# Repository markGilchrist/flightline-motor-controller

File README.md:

# ESP32-S3 12 V Motor PWM Controller (rev 1.0)

A 92 × 76 mm two-layer board that runs a 12 V DC motor from a car battery (11–14.4 V).
An ESP32-S3 sets the motor speed and adds pauses using PWM into a low-side MOSFET.

```
 Car battery ─► J1 ─► 15 A blade fuse ─► TVS (load-dump) ─► reverse-polarity P-FET ─► V12 rail
                                                                                      │
                       ┌──────────── 3.3 V buck (LMR33630) ◄── V12 or USB-C 5 V ──────┤
                       ▼                                                              ▼
                 ESP32-S3-WROOM-1 ── GPIO4 PWM ──► UCC27517 gate driver ──► N-MOSFET ──► J2 MOTOR −
                       │                                                     J2 MOTOR + ◄── V12
                       └── GPIO1 battery-voltage sense, GPIO2 status LED, USB-C for programming
```

## What's in this folder

| File | What it is |
|---|---|
| `motor_ctrl.kicad_pro / .kicad_sch / .kicad_pcb` | KiCad project (opens in KiCad 7, 8 or 9). Ground pours are already filled. |
| `motor_ctrl.kicad_sym`, `sym-lib-table` | The project's schematic symbols, so KiCad finds and can edit them |
| `motor_ctrl_schematic.pdf` | Schematic as a PDF (plotted by KiCad) |
| `fab/gerbers/` | **Ready-to-order** Gerbers, drill files and drill maps |
| `fab/motor_ctrl_pos.csv` | Pick-and-place file (mm, origin at the board's bottom-left corner) |
| `motor_ctrl_BOM.csv` | Bill of materials |
| `board_top.png`, `board_bottom.png` | Renders of the Gerber files (top and bottom copper, silkscreen, drills) |
| `firmware/motor_pwm/motor_pwm.ino` | Arduino sketch: speed program with ramps and pauses |
| `firmware/test/` | Host-side tests for the sketch's logic (`sh firmware/test/run_tests.sh`, needs g++) |

## Key specs

- **Input:** 11–14.4 V car battery. Survives reverse battery (P-MOSFET Q1) and load-dump spikes (SMCJ20CA TVS clamps to about 32 V; everything on the 12 V side is rated 35–45 V).
- **Motor output:** 12 V, up to **10 A continuous**, fused at 15 A. Q2 (IPD90N04S4L-04, 3.8 mΩ) switches the motor's negative lead to ground, so the motor always sees full battery voltage scaled by the duty cycle.
- **PWM:** 20 kHz (silent), 10-bit, from GPIO4 through a UCC27517 4 A gate driver, so the MOSFET switches cleanly from a 3.3 V pin. R5 holds the motor **off** while the ESP32 boots or resets.
- **Freewheel diode:** D3 (STPS20L45CG, 2 × 10 A Schottky) across the motor absorbs the inductive kick at every PWM edge.
- **Logic power:** LMR33630 synchronous buck, 3.3 V / 3 A, runs from the battery or from USB-C. You can program the board on the bench with only a USB cable; the motor won't run without 12 V.
- **Wiper park input:** J5 takes the motor's park-switch contact (12 V tolerant, read on GPIO7), so pauses can stop the blades in the parked position.
- **Extras:** battery-voltage sense on GPIO1 (low/high-voltage cut-out in firmware), status LED on GPIO2, power LED, RESET and BOOT buttons, and a 4-pin AUX header (3V3, GPIO5, GPIO6, GND) for a speed pot, button or sensor.

## Wiring

| Terminal | Pin 1 | Pin 2 |
|---|---|---|
| **J1 BATTERY** | +12 V (from battery +) | GND (battery −) |
| **J2 MOTOR** | MOTOR − | MOTOR + (+12 V) |
| **J5 PARK** | Park-switch contact | GND |

Use wire rated for your motor current (1.5 mm² / 16 AWG for 10 A), keep the battery leads short, and add an inline fuse at the battery end of the + lead as well.

### Using a windscreen wiper motor

- Connect J2 pin 2 (+12 V) to the motor's **low-speed** terminal and J2 pin 1 (MOTOR −) to its **ground/common** terminal. Leave the high-speed terminal unconnected. Terminal numbering varies between makers, so identify them on a bench supply first.
- **Mounting:** the board switches the motor's negative wire. If the motor's ground terminal is connected to its metal case, the case must not touch anything wired to battery negative (a metal frame, a car body). Otherwise the motor gets its ground directly and the board can't stop it. Check with a meter between the ground terminal and the case.
- Typical currents: 2–8 A running, 15–30 A if the arm is jammed or frozen. A jam blows the 15 A fuse within a few seconds, which protects the board.

**Park switch (J5).** With it connected, every pause, `stop` command and the pot turned to zero first runs the wiper on to its park position, then stops.

- **Park contact that closes to ground at park:** wire it between J5 pin 1 and J5 pin 2 (GND).
- **Car-style motor with a 31b park terminal** (it switches between 53a and the motor's ground): wire **31b to J5 pin 1** only. 53a can stay unconnected.
- **Contact that opens at park:** wire it like the first case and set `PARK_INVERT = true` in the sketch.
- To check the wiring, send `v` over USB serial with 12 V connected. It reports the park-input voltage and whether it reads "at park". Move the blades by hand, or run the motor slowly with `s 30`, and watch it change.
- If the firmware never sees the park position within 6 s (for example J5 isn't wired), it stops the motor where it is and prints a warning. Set `USE_PARK = false` if you don't use the park switch.

## Making the board

1. Zip the contents of `fab/gerbers/` and upload it to any PCB service (JLCPCB, PCBWay, OSH Park, Aisler…). Check the preview the fab shows you against `board_top.png` / `board_bottom.png`.
2. Order with **2 oz copper** and 1.6 mm thickness. The 10 A rating depends on the 4 mm power tracks being 2 oz.
3. Board checks already done in KiCad: DRC has no copper, clearance or courtyard errors and no unconnected pads. The only remaining items are four silkscreen warnings from the inductor L1's own library outline, which the fab trims automatically. ERC has 0 errors and 0 warnings, and the schematic and board netlists match.
4. If you change the board in KiCad, press **B** to refill the pours, rerun **Inspect → Design Rules Checker**, and plot new Gerbers with **File → Fabrication Outputs**.
5. All parts are standard footprints from the BOM. The SMD parts are 0603/0805 or larger, so you can hand-solder them. The SO-PowerPAD (U1) and the DPAK/D2PAK tabs need hot air or a hot plate.

## Firmware

1. Arduino IDE → install **esp32 by Espressif** (core 3.x).
2. Board: **ESP32S3 Dev Module**, **USB CDC On Boot: Enabled**.
3. Plug in USB-C. If the port doesn't appear, hold **BOOT**, tap **RESET**, release **BOOT**.
4. Upload `motor_pwm.ino`.

### Using the FlightLine Controller app

The board works with the **FlightLine Controller** app (iOS and Android). It advertises over Bluetooth as **Flightline**, so switch it on and it appears as a card in the app.

- **Off/On (normal cycle):** runs at the set speed for the on time, parks the wiper, waits the off time, and repeats.
- **Quick Burst:** runs continuously at the set speed until you switch it off.
- **Speed, On Time, Off Time sliders:** take effect straight away.
- The board saves the speed, times and Off/On switch, so after a power cut it carries on as it was. Quick Burst always starts off.
- The board shows up in the app as a **Flapper**. To make it a **Magnet** (Off/On just runs at the set speed, with no on/off times) or a **French flapper**, change `FL_DEVICE_TYPE` near the top of the sketch to 2 or 3.

The same commands also work over USB serial (115200 baud), one per line, which is handy for testing without a phone. For example, `aS128` sets the speed to 128/255 and `aS?bb` asks for it back. The full list is at the top of the sketch.

Also over USB: `s 50` runs the motor at 50 % (manual), `stop` parks and stops, `r 500` sets the ramp time for `s` in ms, and `v` prints the battery and park-input voltages, the mode and the Bluetooth state. `go` runs the built-in step program in the `program[]` table (speed, ramp time and hold time per step; speed 0 is a pause). Any app command switches back to app control.

If the battery drops below 10.5 V or rises above 16 V, the motor stops and the status LED blinks fast. It restarts on its own once the battery is back between 11.5 V and 15.5 V, ramping up from zero rather than jumping straight back to speed. On USB power alone the firmware sees no battery, so the motor stays off.

## Before you power it up

- Check the motor's **stall current**. A motor that draws more than about 15 A at start-up will blow the fuse. The MOSFET and diode can handle the surge; the fuse is there to protect the wiring.
- First power-up: use a current-limited bench supply at 12 V, no motor, and check that the 3.3 V rail and the power LED are OK. Then connect the motor.
- The motor's + lead is live whenever the battery is connected. PWM only switches the − side.

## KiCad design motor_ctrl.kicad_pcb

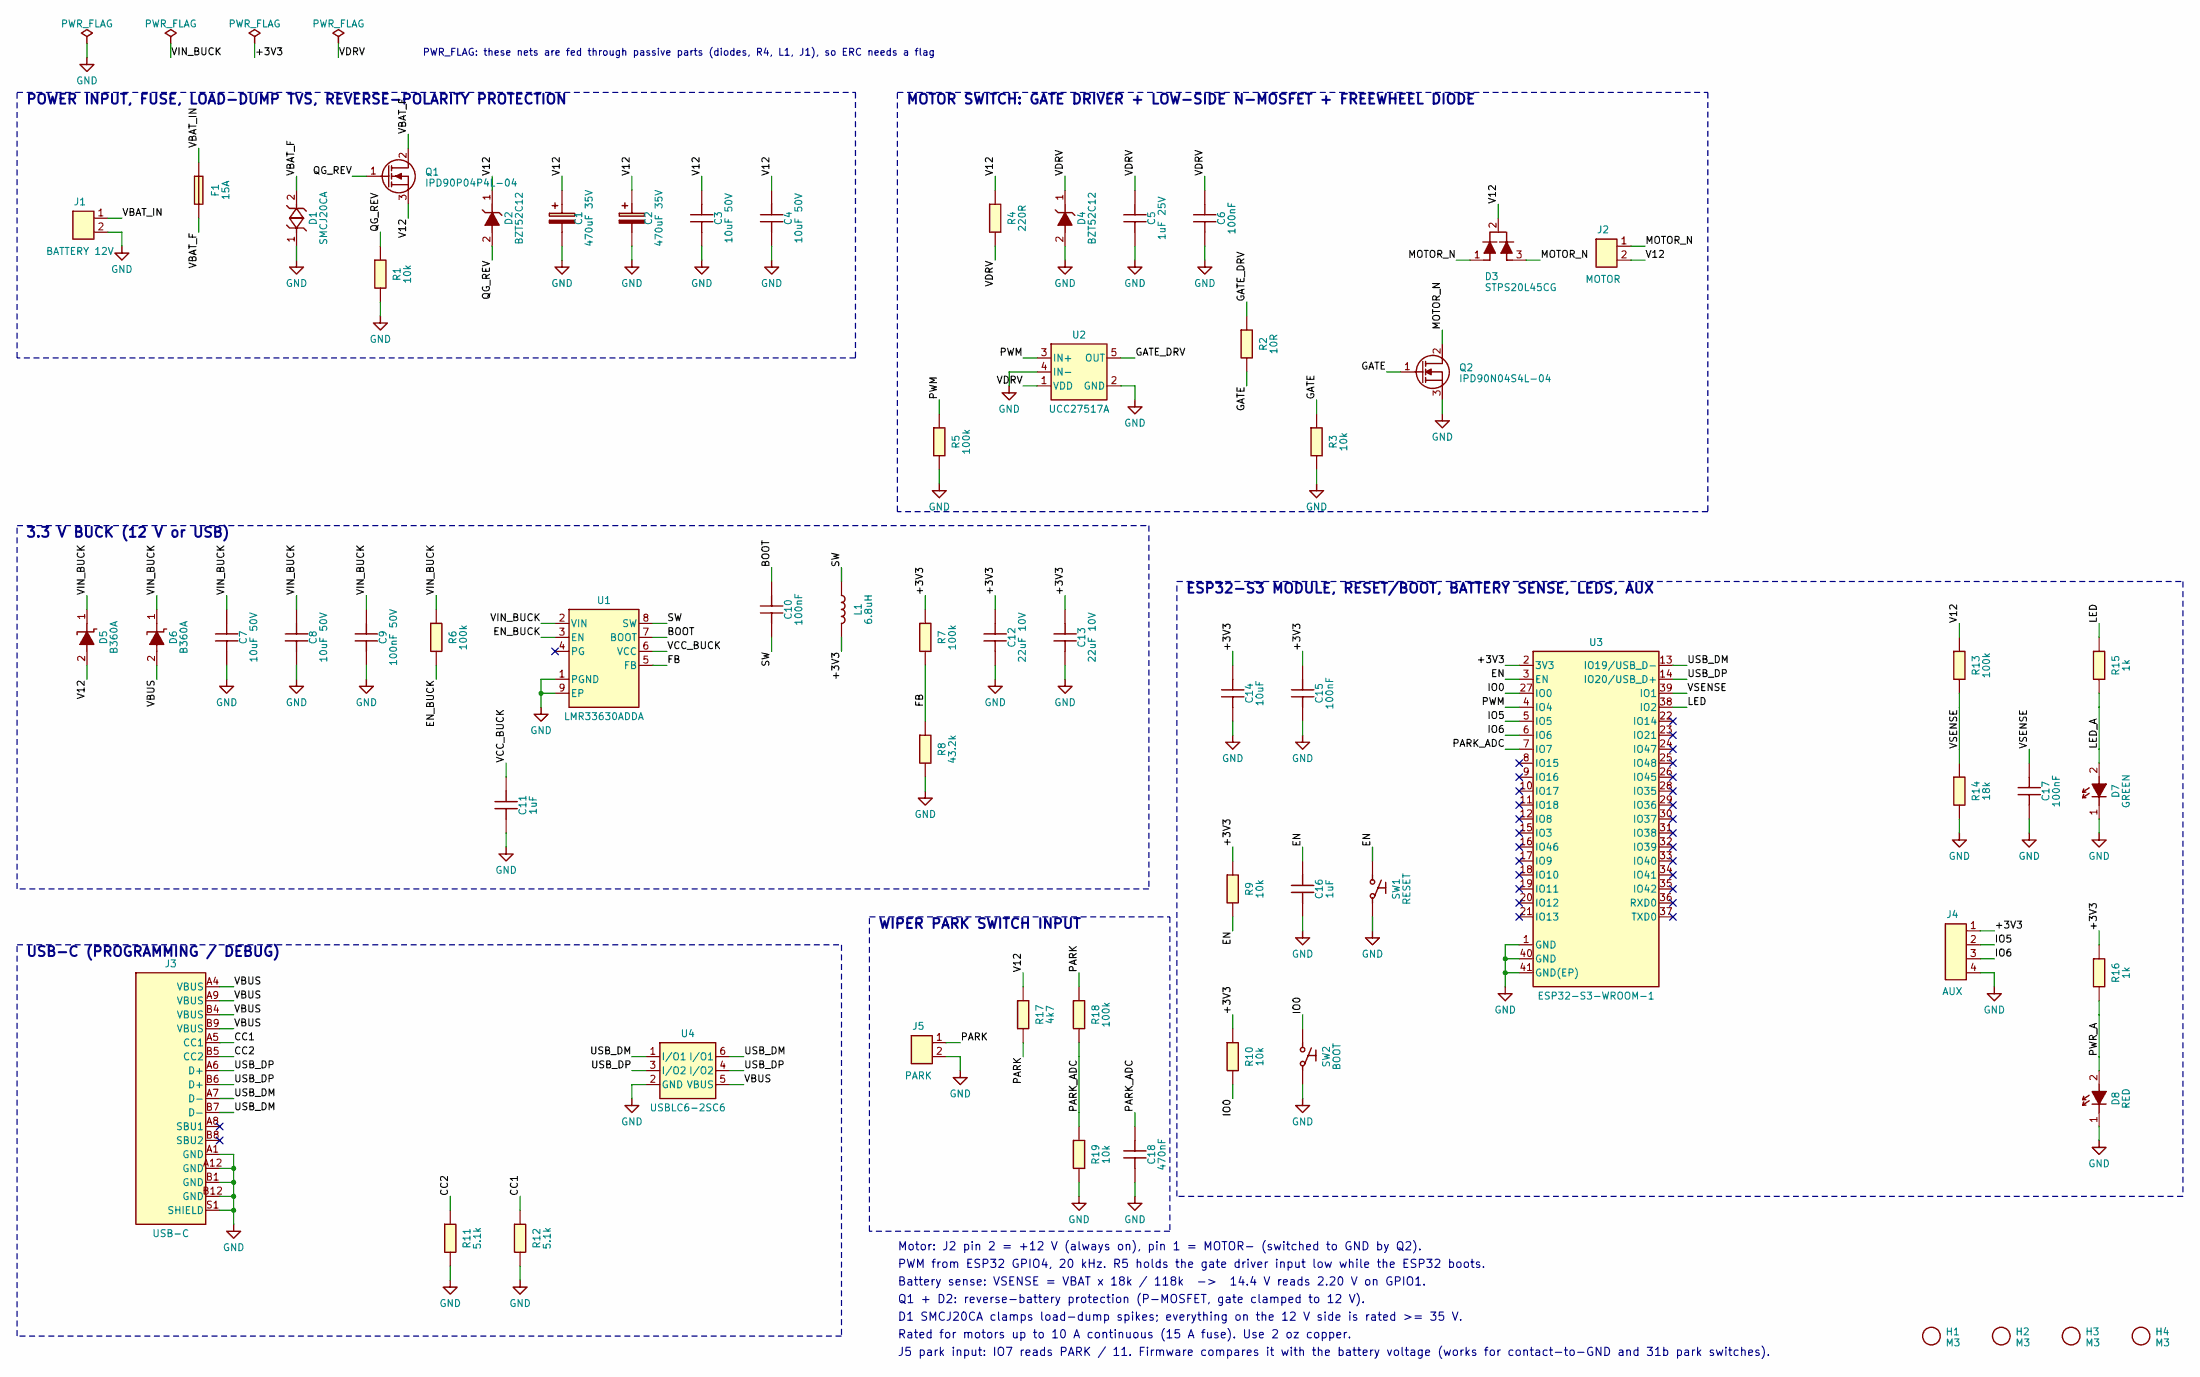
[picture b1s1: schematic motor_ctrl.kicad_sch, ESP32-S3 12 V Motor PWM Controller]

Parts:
C1, C2: 470uF 35V; CP_Radial_D10.0mm_P5.00mm; MPN Panasonic EEU-FR1V471
C3, C4, C7, C8: 10uF 50V; C_1210_3225Metric; MPN X7R 1210
C5: 1uF 25V; C_0805_2012Metric
C6, C10, C15, C17: 100nF; C_0603_1608Metric
C9: 100nF 50V; C_0603_1608Metric
C11, C16: 1uF; C_0603_1608Metric
C12, C13: 22uF 10V; C_1206_3216Metric; MPN X7R 1206
C14: 10uF; C_0805_2012Metric
C18: 470nF; C_0805_2012Metric
D1: SMCJ20CA; D_SMC; MPN Littelfuse SMCJ20CA
D2, D4: BZT52C12; D_SOD-123; MPN BZT52C12
D3: STPS20L45CG; TO-263-2; MPN ST STPS20L45CG-TR
D5, D6: B360A; D_SMA; MPN Diodes B360A-13-F
D7: GREEN; LED_0805_2012Metric
D8: RED; LED_0805_2012Metric
F1: 15A; Fuseholder_Blade_Mini_Keystone_3568; MPN Keystone 3568 + 15A mini blade fuse
H1, H2, H3, H4: M3; MountingHole_3.2mm_M3
J1: BATTERY 12V; TerminalBlock_Phoenix_MKDS-3-2-5.08_1x02_P5.08mm_Horizontal; MPN Phoenix 1711026 (MKDS 3/2-5.08)
J2: MOTOR; TerminalBlock_Phoenix_MKDS-3-2-5.08_1x02_P5.08mm_Horizontal; MPN Phoenix 1711026 (MKDS 3/2-5.08)
J3: USB-C; USB_C_Receptacle_HRO_TYPE-C-31-M-12; MPN HRO TYPE-C-31-M-12
J4: AUX; PinHeader_1x04_P2.54mm_Vertical; MPN 2.54 mm header
J5: PARK; TerminalBlock_Phoenix_PT-1,5-2-3.5-H_1x02_P3.50mm_Horizontal; MPN Phoenix 1984617 (PT 1,5/2-3,5-H)
L1: 6.8uH; L_Bourns_SRP7028A_7.3x6.6mm; MPN Bourns SRP7028A-6R8M
Q1: IPD90P04P4L-04; TO-252-2; MPN Infineon IPD90P04P4L-04
Q2: IPD90N04S4L-04; TO-252-2; MPN Infineon IPD90N04S4L-04
R1, R3, R9, R10: 10k; R_0805_2012Metric
R2: 10R; R_0805_2012Metric
R4: 220R; R_1206_3216Metric
R5, R6: 100k; R_0805_2012Metric
R7, R13, R18: 100k; R_0805_2012Metric; MPN 1%
R8: 43.2k; R_0805_2012Metric; MPN 1%
R11, R12: 5.1k; R_0805_2012Metric
R14: 18k; R_0805_2012Metric; MPN 1%
R15, R16: 1k; R_0805_2012Metric
R17: 4k7; R_1206_3216Metric
R19: 10k; R_0805_2012Metric; MPN 1%
SW1: RESET; SW_SPST_TL3342; MPN E-Switch TL3342F160QG
SW2: BOOT; SW_SPST_TL3342; MPN E-Switch TL3342F160QG
U1: LMR33630ADDA; TI_SO-PowerPAD-8_ThermalVias; MPN TI LMR33630ADDAR
U2: UCC27517A; SOT-23-5; MPN TI UCC27517ADBVR
U3: ESP32-S3-WROOM-1; MPN Espressif ESP32-S3-WROOM-1-N8
U4: USBLC6-2SC6; SOT-23-6; MPN ST USBLC6-2SC6

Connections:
+3V3: C12.1, C13.1, C14.1, C15.1, J4.1, L1.2, R7.1, R9.1, R10.1, R16.1, U3.2 (3V3)
BOOT: C10.1, U1.7 (BOOT)
CC1: J3.A5 (CC1), R12.1
CC2: J3.B5 (CC2), R11.1
EN: C16.1, R9.2, SW1.1, U3.3 (EN)
EN_BUCK: R6.2, U1.3 (EN)
FB: R7.2, R8.1, U1.5 (FB)
GATE: Q2.1 (G), R2.2, R3.1
GATE_DRV: R2.1, U2.5 (OUT)
GND: C1.2, C2.2, C3.1, C4.1, C5.2, C6.1, C7.2, C8.2, C9.2, C11.2, C12.2, C13.2, C14.2, C15.2, C16.2, C17.2, C18.2, D1.1 (A1), D4.2 (A), D7.1 (K), D8.1 (K), J1.2, J3.A1 (GND), J3.A12 (GND), J3.B1 (GND), J3.B12 (GND), J3.S1 (SHIELD), J4.4, J5.2, Q2.3 (S), R1.2, R3.2, R5.2, R8.2, R11.2, R12.2, R14.2, R19.2, SW1.2, SW2.2, U1.1 (PGND), U1.9 (EP), U2.2 (GND), U2.4 (IN-), U3.1 (GND), U3.40 (GND), U3.41 (GND(EP)), U4.2 (GND)
IO0: R10.2, SW2.1, U3.27 (IO0)
IO5: J4.2, U3.5 (IO5)
IO6: J4.3, U3.6 (IO6)
LED: R15.1, U3.38 (IO2)
LED_A: D7.2 (A), R15.2
MOTOR_N: D3.1 (A1), D3.3 (A2), J2.1, Q2.2 (D)
PARK: J5.1, R17.2, R18.1
PARK_ADC: C18.1, R18.2, R19.1, U3.7 (IO7)
PWM: R5.1, U2.3 (IN+), U3.4 (IO4)
PWR_A: D8.2 (A), R16.2
QG_REV: D2.2 (A), Q1.1 (G), R1.1
SW: C10.2, L1.1, U1.8 (SW)
USB_DM: J3.A7 (D-), J3.B7 (D-), U3.13 (IO19/USB_D-), U4.1 (I/O1), U4.6 (I/O1)
USB_DP: J3.A6 (D+), J3.B6 (D+), U3.14 (IO20/USB_D+), U4.3 (I/O2), U4.4 (I/O2)
V12: C1.1, C2.1, C3.2, C4.2, D2.1 (K), D3.2 (K), D5.2 (A), J2.2, Q1.3 (S), R4.1, R13.1, R17.1
VBAT_F: D1.2 (A2), F1.2, Q1.2 (D)
VBAT_IN: F1.1, J1.1
VBUS: D6.2 (A), J3.A4 (VBUS), J3.A9 (VBUS), J3.B4 (VBUS), J3.B9 (VBUS), U4.5 (VBUS)
VCC_BUCK: C11.1, U1.6 (VCC)
VDRV: C5.1, C6.2, D4.1 (K), R4.2, U2.1 (VDD)
VIN_BUCK: C7.1, C8.1, C9.1, D5.1 (K), D6.1 (K), R6.1, U1.2 (VIN)
VSENSE: C17.1, R13.2, R14.1, U3.39 (IO1)

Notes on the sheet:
PWR_FLAG: these nets are fed through passive parts (diodes, R4, L1, J1), so ERC needs a flag
POWER INPUT, FUSE, LOAD-DUMP TVS, REVERSE-POLARITY PROTECTION
MOTOR SWITCH: GATE DRIVER + LOW-SIDE N-MOSFET + FREEWHEEL DIODE
3.3 V BUCK (12 V or USB)
ESP32-S3 MODULE, RESET/BOOT, BATTERY SENSE, LEDS, AUX
USB-C (PROGRAMMING / DEBUG)
WIPER PARK SWITCH INPUT
Motor: J2 pin 2 = +12 V (always on), pin 1 = MOTOR- (switched to GND by Q2).
PWM from ESP32 GPIO4, 20 kHz. R5 holds the gate driver input low while the ESP32 boots.
Battery sense: VSENSE = VBAT x 18k / 118k -> 14.4 V reads 2.20 V on GPIO1.
Q1 + D2: reverse-battery protection (P-MOSFET, gate clamped to 12 V).
D1 SMCJ20CA clamps load-dump spikes; everything on the 12 V side is rated >= 35 V.
Rated for motors up to 10 A continuous (15 A fuse). Use 2 oz copper.
J5 park input: IO7 reads PARK / 11. Firmware compares it with the battery voltage (works for contact-to-GND and 31b park switches).

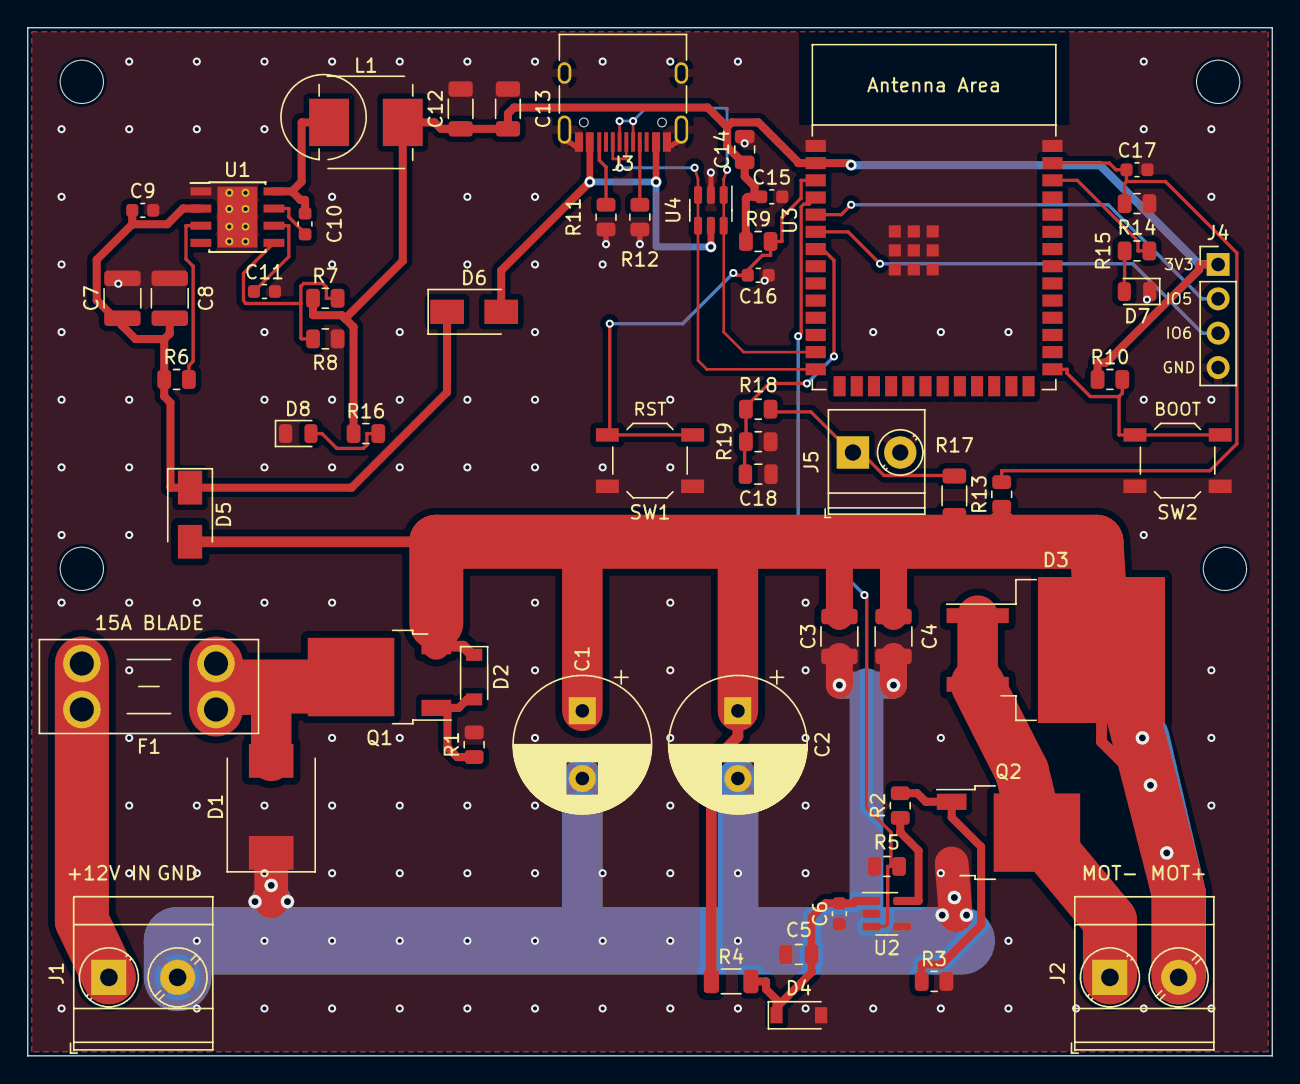
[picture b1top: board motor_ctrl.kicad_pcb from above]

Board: 2 copper layers, 92.0 x 76.0 mm, 64 parts (0 on the bottom side), 32 nets.

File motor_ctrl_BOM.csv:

Qty,References,Value,Footprint,Manufacturer part / notes
2,C1 C2,470uF 35V,CP_Radial_D10.0mm_P5.00mm,Panasonic EEU-FR1V471
4,C3 C4 C7 C8,10uF 50V,C_1210_3225Metric,X7R 1210
1,C5,1uF 25V,C_0805_2012Metric,
4,C6 C10 C15 C17,100nF,C_0603_1608Metric,
1,C9,100nF 50V,C_0603_1608Metric,
2,C11 C16,1uF,C_0603_1608Metric,
2,C12 C13,22uF 10V,C_1206_3216Metric,X7R 1206
1,C14,10uF,C_0805_2012Metric,
1,C18,470nF,C_0805_2012Metric,
1,D1,SMCJ20CA,D_SMC,Littelfuse SMCJ20CA
2,D2 D4,BZT52C12,D_SOD-123,BZT52C12
1,D3,STPS20L45CG,TO-263-2,ST STPS20L45CG-TR
2,D5 D6,B360A,D_SMA,Diodes B360A-13-F
1,D7,GREEN,LED_0805_2012Metric,
1,D8,RED,LED_0805_2012Metric,
1,F1,15A,Fuseholder_Blade_Mini_Keystone_3568,Keystone 3568 + 15A mini blade fuse
1,J1,BATTERY 12V,TerminalBlock_Phoenix_MKDS-3-2-5.08_1x02_P5.08mm_Horizontal,Phoenix 1711026 (MKDS 3/2-5.08)
1,J2,MOTOR,TerminalBlock_Phoenix_MKDS-3-2-5.08_1x02_P5.08mm_Horizontal,Phoenix 1711026 (MKDS 3/2-5.08)
1,J3,USB-C,USB_C_Receptacle_HRO_TYPE-C-31-M-12,HRO TYPE-C-31-M-12
1,J4,AUX,PinHeader_1x04_P2.54mm_Vertical,2.54 mm header
1,J5,PARK,"TerminalBlock_Phoenix_PT-1,5-2-3.5-H_1x02_P3.50mm_Horizontal","Phoenix 1984617 (PT 1,5/2-3,5-H)"
1,L1,6.8uH,L_Bourns_SRP7028A_7.3x6.6mm,Bourns SRP7028A-6R8M
1,Q1,IPD90P04P4L-04,TO-252-2,Infineon IPD90P04P4L-04
1,Q2,IPD90N04S4L-04,TO-252-2,Infineon IPD90N04S4L-04
4,R1 R3 R9 R10,10k,R_0805_2012Metric,
1,R2,10R,R_0805_2012Metric,
1,R4,220R,R_1206_3216Metric,
2,R5 R6,100k,R_0805_2012Metric,
3,R7 R13 R18,100k,R_0805_2012Metric,1%
1,R8,43.2k,R_0805_2012Metric,1%
2,R11 R12,5.1k,R_0805_2012Metric,
1,R14,18k,R_0805_2012Metric,1%
2,R15 R16,1k,R_0805_2012Metric,
1,R17,4k7,R_1206_3216Metric,
1,R19,10k,R_0805_2012Metric,1%
1,SW1,RESET,SW_SPST_TL3342,E-Switch TL3342F160QG
1,SW2,BOOT,SW_SPST_TL3342,E-Switch TL3342F160QG
1,U1,LMR33630ADDA,TI_SO-PowerPAD-8_ThermalVias,TI LMR33630ADDAR
1,U2,UCC27517A,SOT-23-5,TI UCC27517ADBVR
1,U3,ESP32-S3-WROOM-1,ESP32-S3-WROOM-1,Espressif ESP32-S3-WROOM-1-N8
1,U4,USBLC6-2SC6,SOT-23-6,ST USBLC6-2SC6
